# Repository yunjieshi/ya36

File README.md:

# YA36 - Yet Another 36 Keys Split-Ergo Keyboard With Tight Key Spacing and Angled Columns

YA36 is a 36 keys split-ergo low-profile keyboard designed to fit my own (strange shaped) hand. Although I don't think any other people can type on this specific design comfortably, there are some findings I think may worth sharing.

## Why angled columns
The idea of angled columns comes from an observation I made when I considering a question "why no matter how much I increase the pinky stagger or decrease the key spacing, I could never comfortably reach the top row pinky key," which is moving the fingers (except middle) straight upward is very unnatural. If you try to make a fist and then release it, you will find your finger moving along an angle. Thus I think making the columns angled may lead to a more natural muscle movement. Then to figure out how much I should angle the columns (and also the amount of column stagger), I dipped my fingers into some pigments and simulated typing on a sheet of paper (but instead of following the normal keyboard layout, I let my fingers stretch naturally). The result is about 8 degrees between two adjective fingers, and the middle finger worked as the centerline (i.e. no angle, parallel to the forearm). Because of this design, reaching the top row pinky key is now effortless, reaching the top row keys of index and ring fingers is also become easier, and surprisingly because the key spacing is reduced, reaching the extra index column is not difficult (if not easier) even with the angle.

## Reduced key spacing
Usually the spacing between the keys on most of the keyboards is 19.05 mm (or 18 x 17 mm for choc switch), but since every person has a different hand size, you may find that the standard key spacing may not suitable for everyone. This is especially a problem for me since I have a very small hand (16 cm length). When using a normal keyboard, I always found I'm tapping on the edge of the top and bottom row keycaps instead of the center, which is uncomfortable especially for those sculptured profiles. After testing several different key spacings, I found that the 15 mm spacing (the smallest possible spacing for choc switch) works best for me.  However, one thing that needs to notice is that the smaller the key spacing is, the more accurate the column stagger need to be. The reason is that the area of the top surface of the keycap would become smaller because of the smaller key spacing, which means that it would not be as tolerant as the bigger keycaps when you cannot tap on the center of the keycap (i.e. tap on the wrong key vs. tap on edge). So if you have a small hand but have a bad experience typing on a small key spacing keyboard (like the one on a laptop), it may not be the fault of the key spacing itself but the problem of the non-ergo layout.

## Why the index column is higher than the middle column
Because my index finger is longer than the ring finger, and it naturally located at a higher position than my middle finger when I curled my fingers and lay them on a flat surface. However, what I want to say is that sometimes we would stick to the 'common' design and didn't notice that our own hand may very different from other people's. When I just started to design my own keyboard, I always place the index column lower than the middle column, and only tried to figure out how much lower it should be, because all the column stagger keyboards I saw looks like this. Unfortunately it does not work for me. My index finger always feels that it is not in the correct position. But one day when I looked at my curled up fingers, I suddenly notice that my index finger is higher than the middle finger. Although I'm not very sure if a higher index column would work or not, I anyway gave it a try, and the result turned out very good.

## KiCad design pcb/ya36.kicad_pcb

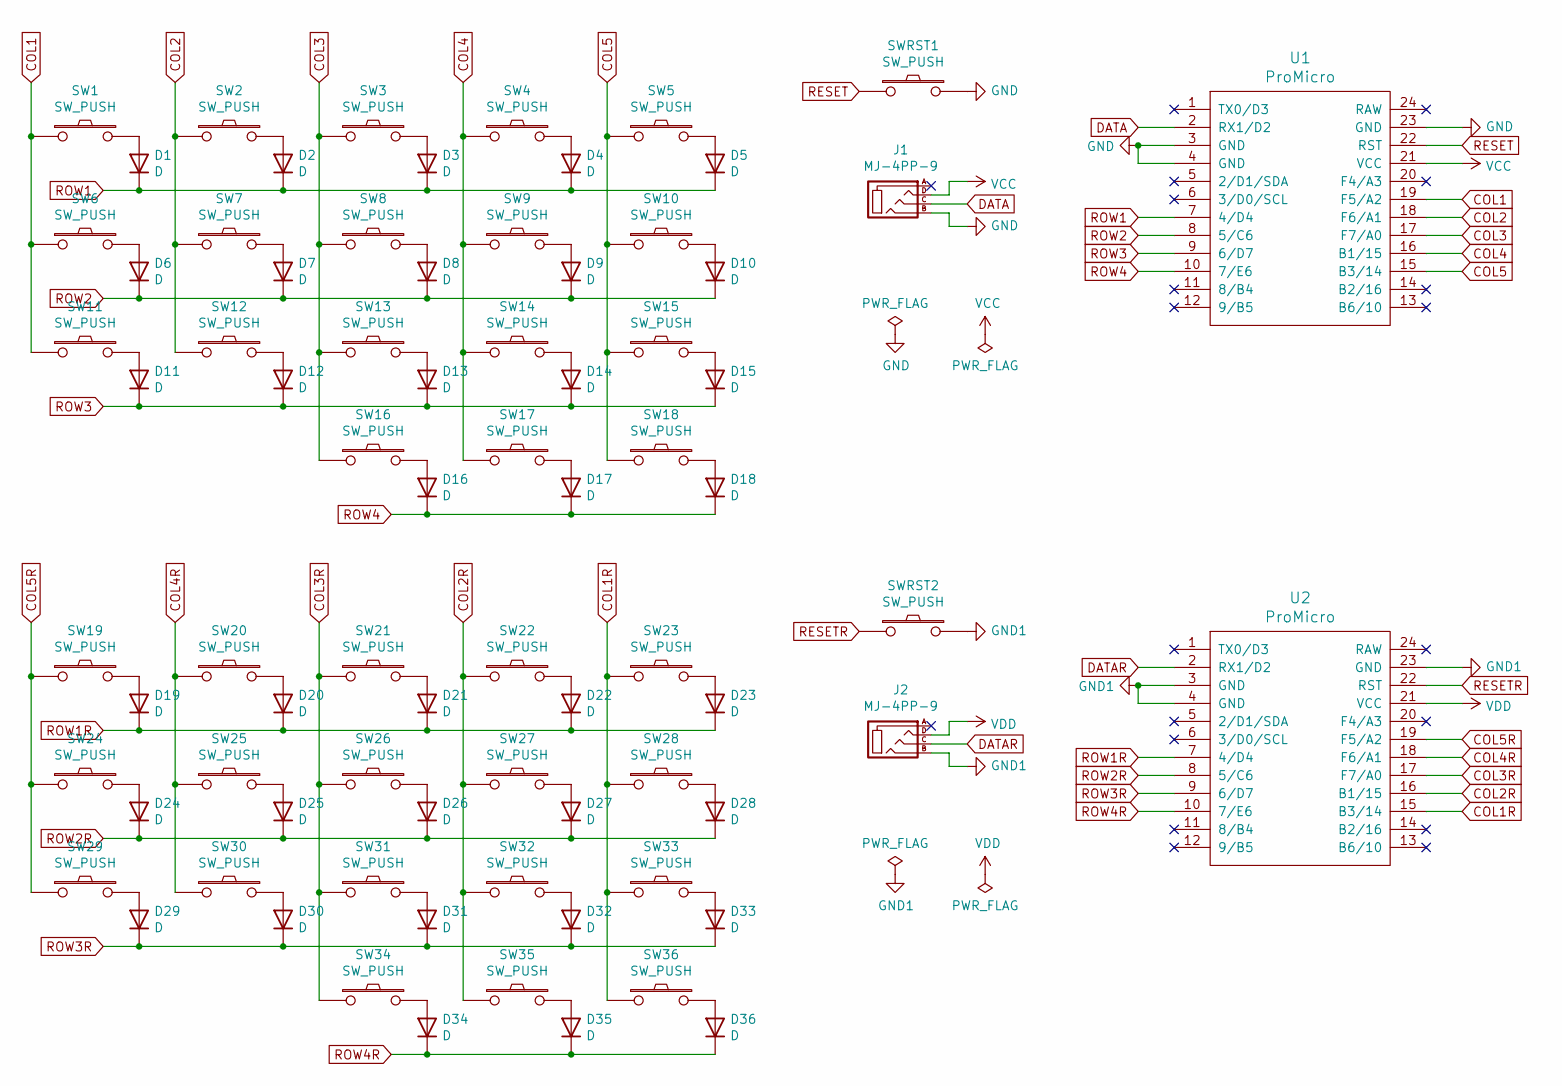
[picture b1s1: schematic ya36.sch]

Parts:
D1, D2, D3, D4, D5, D6, D7, D8, D9, D10, D11, D12, D13, D14, D15, D16, D17, D18, D19, D20, D21, D22, D23, D24, D25, D26, D27, D28, D29, D30, D31, D32, D33, D34, D35, D36: D; D3_SMD_v2
J1, J2: MJ-4PP-9; MJ-4PP-9_1side
SW1, SW2, SW3, SW4, SW5, SW6, SW7, SW8, SW9, SW10, SW11, SW12, SW13, SW14, SW15, SW16, SW17, SW18, SW19, SW20, SW21, SW22, SW23, SW24, SW25, SW26, SW27, SW28, SW29, SW30, SW31, SW32, SW33, SW34, SW35, SW36: SW_PUSH; Kailh_socket_PG1350
SWRST1, SWRST2: SW_PUSH; ResetSW
U1, U2: ProMicro; ProMicro_v3.5

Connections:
COL1: SW1.1, SW6.1, SW11.1, U1.19 (F5/A2)
COL1R: SW23.1, SW28.1, SW33.1, SW36.1, U2.15 (B3/14)
COL2: SW2.1, SW7.1, SW12.1, U1.18 (F6/A1)
COL2R: SW22.1, SW27.1, SW32.1, SW35.1, U2.16 (B1/15)
COL3: SW3.1, SW8.1, SW13.1, SW16.1, U1.17 (F7/A0)
COL3R: SW21.1, SW26.1, SW31.1, SW34.1, U2.17 (F7/A0)
COL4: SW4.1, SW9.1, SW14.1, SW17.1, U1.16 (B1/15)
COL4R: SW20.1, SW25.1, SW30.1, U2.18 (F6/A1)
COL5: SW5.1, SW10.1, SW15.1, SW18.1, U1.15 (B3/14)
COL5R: SW19.1, SW24.1, SW29.1, U2.19 (F5/A2)
DATA: J1.C, U1.2 (RX1/D2)
DATAR: J2.C, U2.2 (RX1/D2)
GND: J1.B, SWRST1.2, U1.3 (GND), U1.4 (GND), U1.23 (GND)
GND1: J2.B, SWRST2.2, U2.3 (GND), U2.4 (GND), U2.23 (GND)
unnamed: D1.2 (A), SW1.2
unnamed: D2.2 (A), SW2.2
unnamed: D3.2 (A), SW3.2
unnamed: D4.2 (A), SW4.2
unnamed: D5.2 (A), SW5.2
unnamed: D6.2 (A), SW6.2
unnamed: D7.2 (A), SW7.2
unnamed: D8.2 (A), SW8.2
unnamed: D9.2 (A), SW9.2
unnamed: D10.2 (A), SW10.2
unnamed: D11.2 (A), SW11.2
unnamed: D12.2 (A), SW12.2
unnamed: D13.2 (A), SW13.2
unnamed: D14.2 (A), SW14.2
unnamed: D15.2 (A), SW15.2
unnamed: D16.2 (A), SW16.2
unnamed: D17.2 (A), SW17.2
unnamed: D18.2 (A), SW18.2
unnamed: D19.2 (A), SW19.2
unnamed: D20.2 (A), SW20.2
unnamed: D21.2 (A), SW21.2
unnamed: D22.2 (A), SW22.2
unnamed: D23.2 (A), SW23.2
unnamed: D24.2 (A), SW24.2
unnamed: D25.2 (A), SW25.2
unnamed: D26.2 (A), SW26.2
unnamed: D27.2 (A), SW27.2
unnamed: D28.2 (A), SW28.2
unnamed: D29.2 (A), SW29.2
unnamed: D30.2 (A), SW30.2
unnamed: D31.2 (A), SW31.2
unnamed: D32.2 (A), SW32.2
unnamed: D33.2 (A), SW33.2
unnamed: D34.2 (A), SW34.2
unnamed: D35.2 (A), SW35.2
unnamed: D36.2 (A), SW36.2
RESET: SWRST1.1, U1.22 (RST)
RESETR: SWRST2.1, U2.22 (RST)
ROW1: D1.1 (K), D2.1 (K), D3.1 (K), D4.1 (K), D5.1 (K), U1.7 (4/D4)
ROW1R: D19.1 (K), D20.1 (K), D21.1 (K), D22.1 (K), D23.1 (K), U2.7 (4/D4)
ROW2: D6.1 (K), D7.1 (K), D8.1 (K), D9.1 (K), D10.1 (K), U1.8 (5/C6)
ROW2R: D24.1 (K), D25.1 (K), D26.1 (K), D27.1 (K), D28.1 (K), U2.8 (5/C6)
ROW3: D11.1 (K), D12.1 (K), D13.1 (K), D14.1 (K), D15.1 (K), U1.9 (6/D7)
ROW3R: D29.1 (K), D30.1 (K), D31.1 (K), D32.1 (K), D33.1 (K), U2.9 (6/D7)
ROW4: D16.1 (K), D17.1 (K), D18.1 (K), U1.10 (7/E6)
ROW4R: D34.1 (K), D35.1 (K), D36.1 (K), U2.10 (7/E6)
VCC: J1.D, U1.21 (VCC)
VDD: J2.D, U2.21 (VCC)

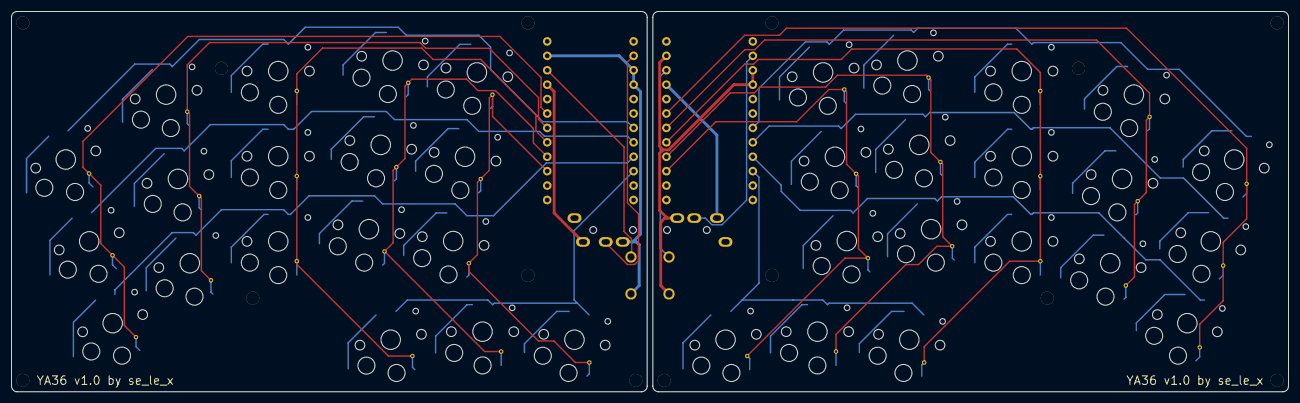
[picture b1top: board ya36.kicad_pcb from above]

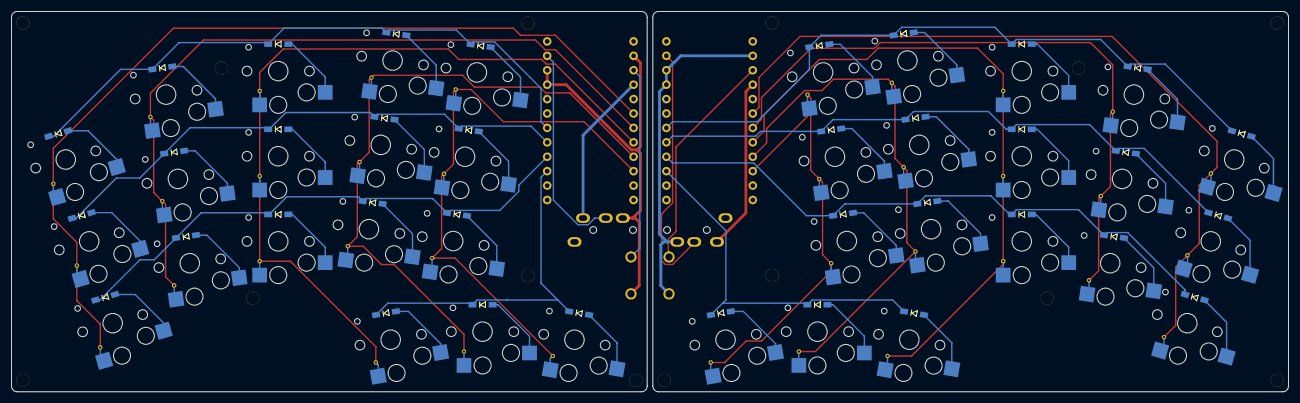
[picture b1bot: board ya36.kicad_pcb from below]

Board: 2 copper layers, 225.0 x 67.0 mm, 92 parts (36 on the bottom side), 62 nets.

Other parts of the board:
Ref**: Val**; M2_Threads_v2
Ref**#2, Ref**#3, Ref**#4, Ref**#5, Ref**#6, Ref**#7, Ref**#8, Ref**#9, Ref**#10, Ref**#11, Ref**#12, Ref**#13, Ref**#14: Val**; M2_Threads_v2

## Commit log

2021-03-04 Add pcb
2021-03-04 Update library
2021-03-06 Update route
2021-03-06 Update pcb
2021-03-06 Generate Gerber files
2021-03-06 Update Gerber
2021-03-06 Separate Gerber
2021-03-16 Update gbr
2021-03-24 Update fp-info-cache
2021-03-24 Upload images
